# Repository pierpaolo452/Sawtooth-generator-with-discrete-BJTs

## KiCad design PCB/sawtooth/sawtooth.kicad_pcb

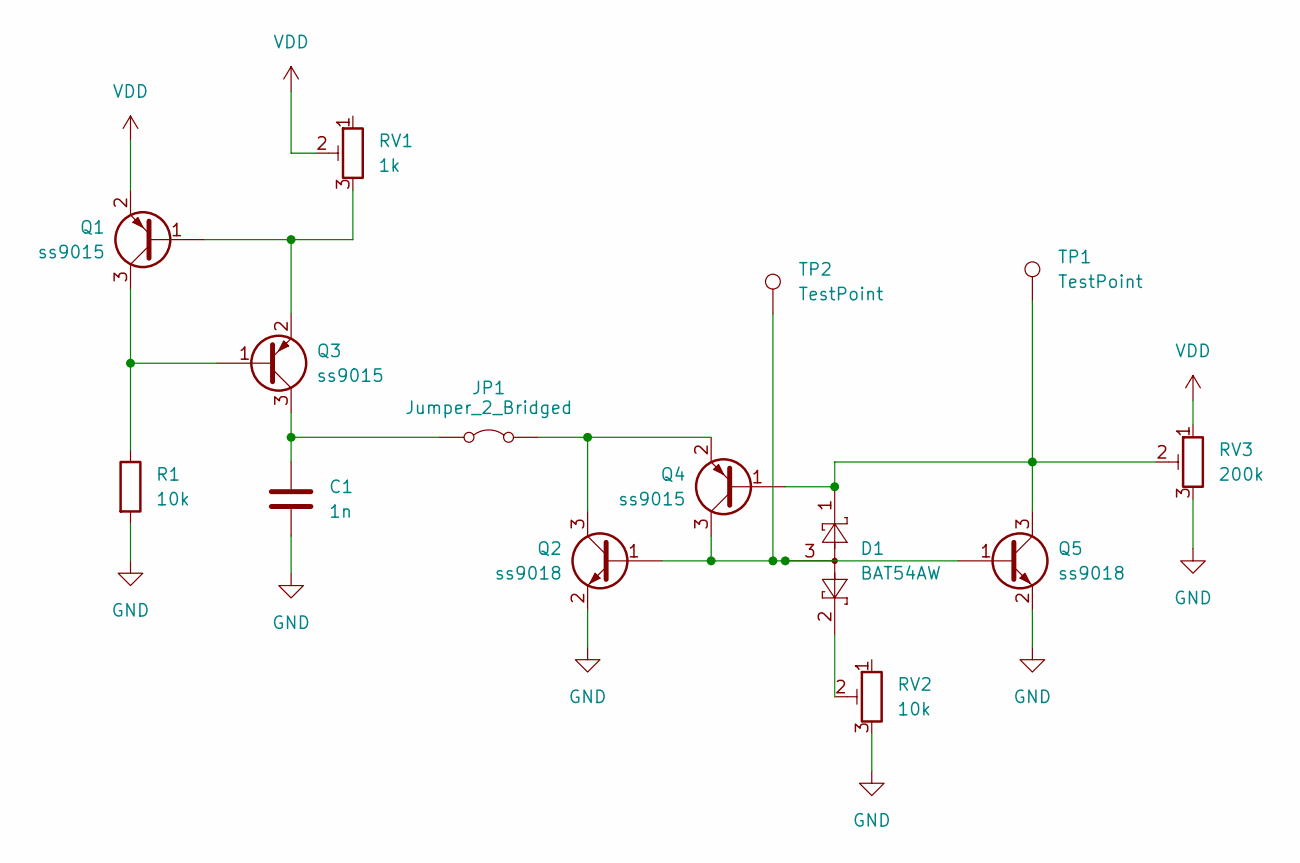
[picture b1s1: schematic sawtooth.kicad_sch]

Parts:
C1: 1n; C_0805_2012Metric_Pad1.18x1.45mm_HandSolder
D1: BAT54AW; SOT-323_SC-70
JP1: Jumper_2_Bridged; TestPoint_2Pads_Pitch2.54mm_Drill0.8mm
Q1, Q3, Q4: ss9015; SOT-23
Q2, Q5: ss9018; SOT-23
R1: 10k; R_0805_2012Metric_Pad1.20x1.40mm_HandSolder
RV1: 1k; Potentiometer_ACP_CA9-H5_Horizontal; LCSC C118929
RV2: 10k; Potentiometer_ACP_CA9-H5_Horizontal; LCSC C118929
RV3: 200k; Potentiometer_ACP_CA9-H5_Horizontal; LCSC C118929
TP1, TP2: TestPoint; Pin_D0.7mm_L6.5mm_W1.8mm_FlatFork

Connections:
GND: C1.2, Q2.2 (E), Q5.2 (E), R1.2, RV2.3, RV3.3
unnamed: D1.2, RV2.2
unnamed: C1.1, JP1.1 (A), Q3.3 (C)
unnamed: JP1.2 (B), Q2.3 (C), Q4.2 (E)
unnamed: Q1.1 (B), Q3.2 (E), RV1.3
unnamed: Q1.3 (C), Q3.1 (B), R1.1
unnamed: D1.3, Q2.1 (B), Q4.3 (C), Q5.1 (B), TP2.1
unnamed: D1.1, Q4.1 (B), Q5.3 (C), RV3.2, TP1.1
VDD: Q1.2 (E), RV1.2, RV3.1

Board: 2 copper layers, 13 parts (0 on the bottom side), 9 nets, no tracks yet.

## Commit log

2025-11-28 Begin
